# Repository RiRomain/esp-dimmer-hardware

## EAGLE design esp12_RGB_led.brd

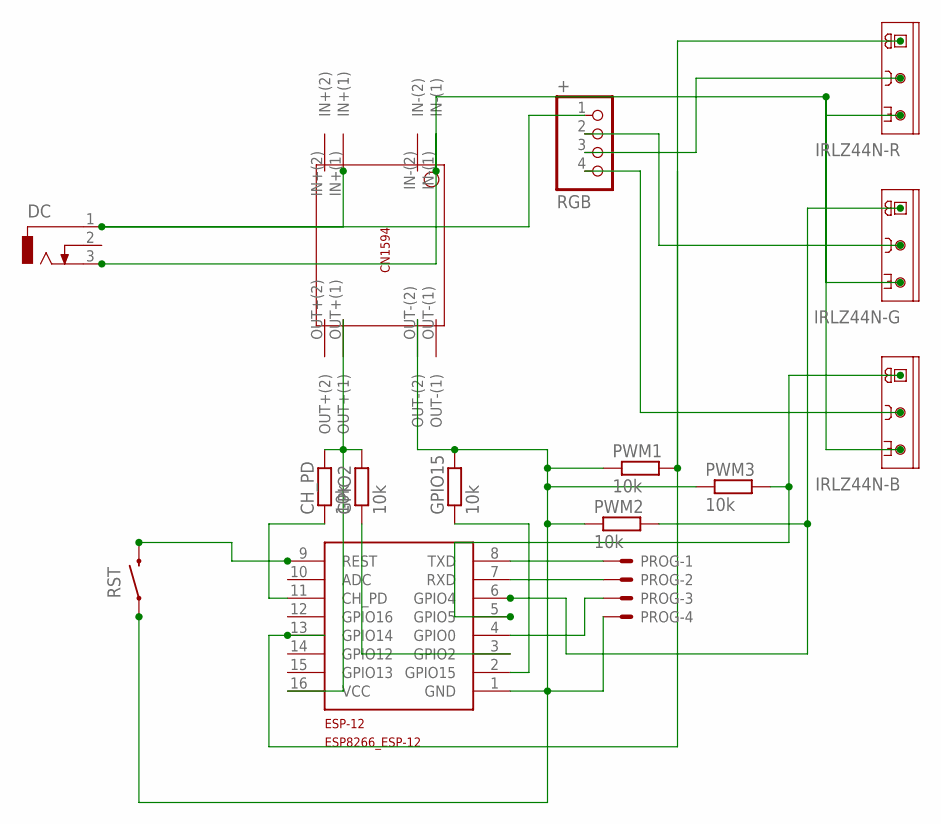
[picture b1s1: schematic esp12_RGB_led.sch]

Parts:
+: RGB; 1X04
CH_PD: 10k; R0603
DC: DCJ0202
DC_CONVERTER: CN1594THROUGH-HOLE; CN1594
ESP-12: ESP8266_ESP-12; ESP8266-ESP12
GPIO2, GPIO15: 10k; R0603
IRLZ44N-B, IRLZ44N-G, IRLZ44N-R: TIP121; TO220AV
PROG: 87438-04
PWM1, PWM2, PWM3: 10k; R0603
RST: SWITCH-MOMENTARY-2SMD-1101NE; TACTILE-SWITCH-1101NE

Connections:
3.3V: CH_PD.2, DC_CONVERTER.OUT+(1), ESP-12.16 (VCC), GPIO2.2
GND: DC.3, DC_CONVERTER.IN-(1), IRLZ44N-B.E, IRLZ44N-G.E, IRLZ44N-R.E
GND3.3V: DC_CONVERTER.OUT-(2), ESP-12.1 (GND), GPIO15.2, PROG.4, PWM1.1, PWM2.1, PWM3.1, RST.1
unnamed: CH_PD.1, ESP-12.11 (CH_PD)
unnamed: ESP-12.3 (GPIO2), GPIO2.1
unnamed: +.3, IRLZ44N-R.C
unnamed: ESP-12.8 (TXD), PROG.1
unnamed: ESP-12.2 (GPIO15), GPIO15.1
unnamed: ESP-12.7 (RXD), PROG.2
unnamed: ESP-12.4 (GPIO0), PROG.3
unnamed: +.2, IRLZ44N-G.C
unnamed: +.4, IRLZ44N-B.C
unnamed: ESP-12.9 (REST), RST.2
unnamed: +.1, DC.1, DC_CONVERTER.IN+(1)
unnamed: ESP-12.13 (GPIO14), IRLZ44N-R.B, PWM1.2
unnamed: ESP-12.6 (GPIO4), IRLZ44N-G.B, PWM2.2
unnamed: ESP-12.5 (GPIO5), IRLZ44N-B.B, PWM3.2

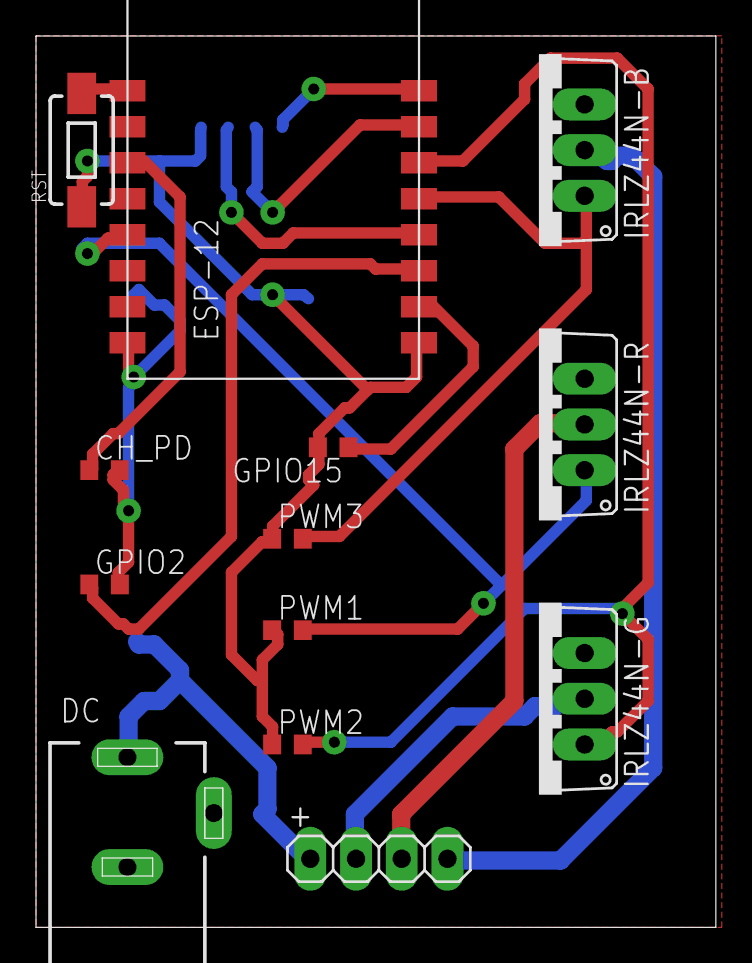
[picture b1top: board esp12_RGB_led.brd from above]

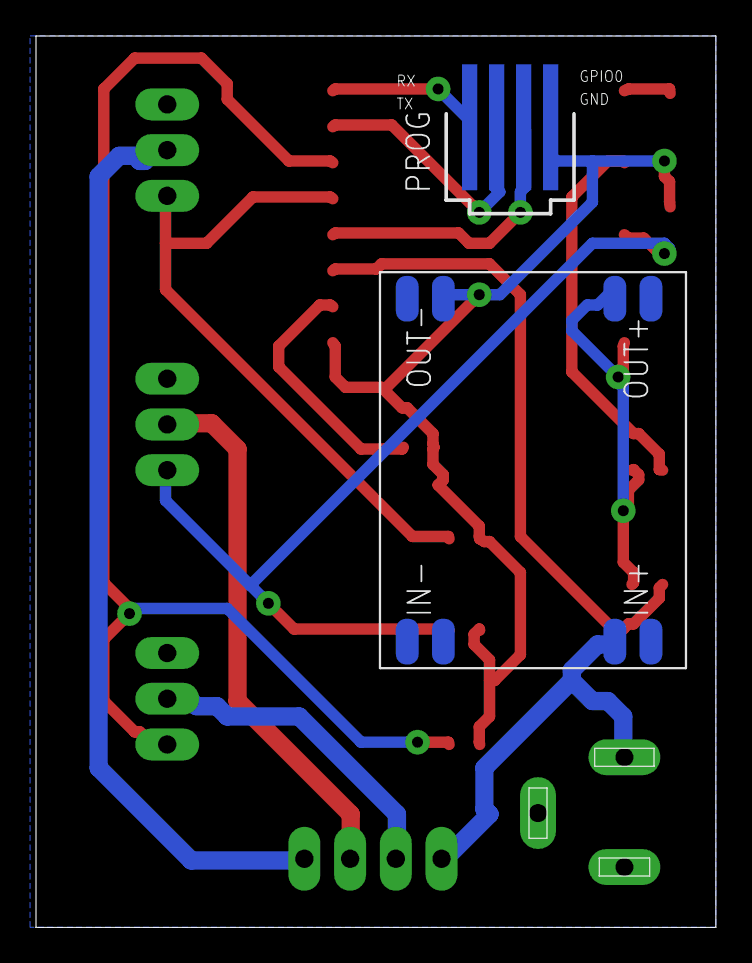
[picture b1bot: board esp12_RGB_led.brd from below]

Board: 2 copper layers, 37.8 x 49.5 mm, 15 parts (2 on the bottom side), 17 nets.

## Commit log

2015-09-07 RGB Board
    First version of the board with RGB channel.
    Mosfet replace by some IRLZ44N.
    Terminal block replace by pin header.
    Use GPIO 4, 5 and 14.
2015-10-25 Sikscreen correction
    Correction of the Silk-Screen, RX, TX, GPIO und GND a little bit off on
    the previous version.
2015-10-25 New photo
    Addition of board and programming tools photo
2015-10-25 PCB Rendering + Schema
    Addition of the electrical schema and the PCB 2D Rendering. (Silk-screen
    RX marking still off on this version)

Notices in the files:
parts and their libraries:
SparkFun-Electromechanical: Licensing: Creative Commons ShareAlike 4.0 International - https://creativecommons.org/licenses/by-sa/4.0
